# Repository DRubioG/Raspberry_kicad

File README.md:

# Raspberry_kicad
 Raspberry  Pi 4 in Kicad

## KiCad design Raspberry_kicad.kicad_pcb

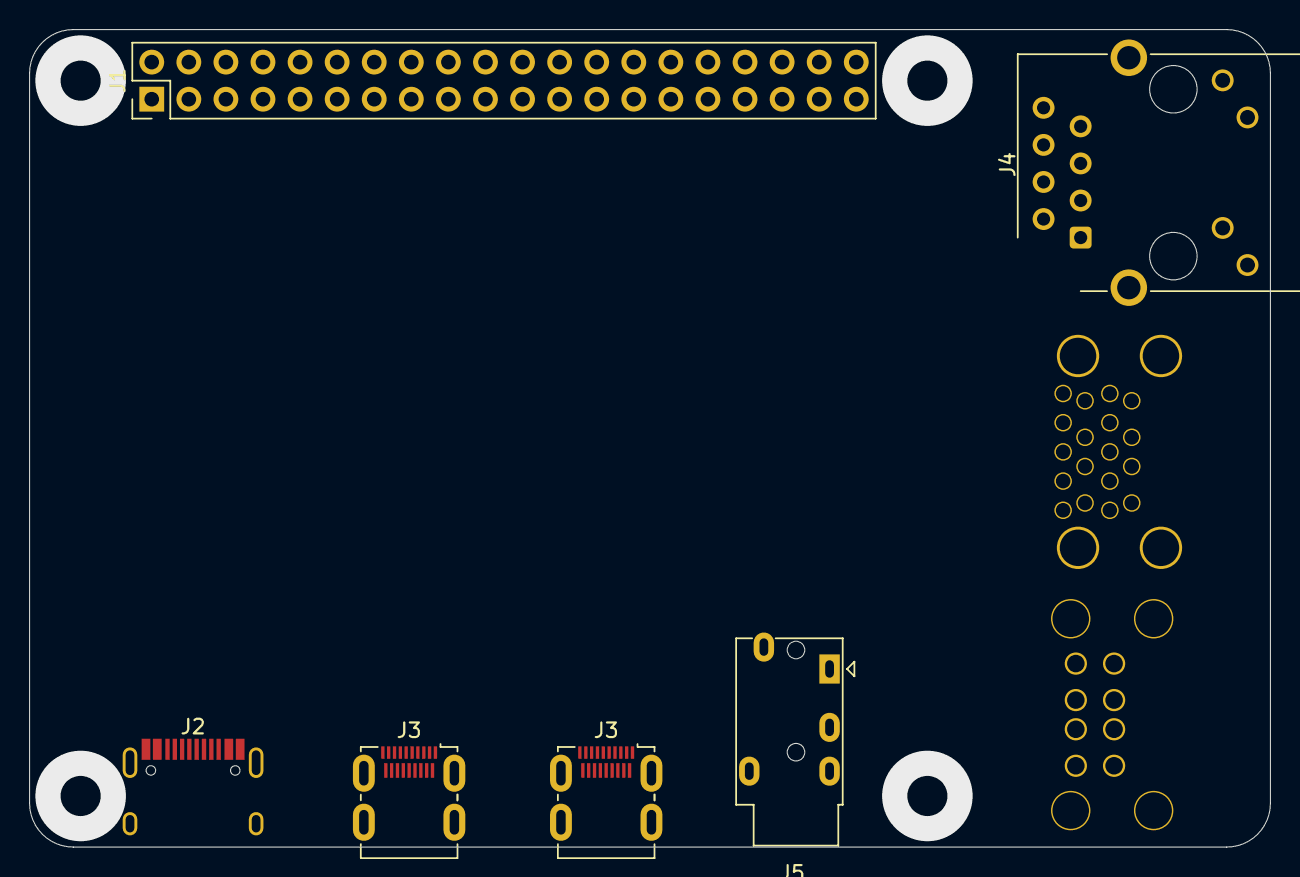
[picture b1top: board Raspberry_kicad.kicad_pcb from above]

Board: 2 copper layers, 85.0 x 56.0 mm, 9 parts (1 on the bottom side), 20 nets, no tracks yet.

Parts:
J1: Conn_02x20_Top_Bottom; PinHeader_2x20_P2.54mm_Vertical
J2: usb_type_c; HRO-TYPE-C-31-M-12-Assembly
J3, J3#2: HDMI_D_1.4; HDMI_Micro-D_Molex_46765-1x01
J4: RJ45_LED; RJ45_Cetus_J1B1211CCD_Horizontal
J5: AudioJack4_Ground; Jack_3.5mm_PJ320E_Horizontal
J6: Micro_SD_Card; microSD_HC_Molex_104031-0811
U1: USB_3_0_HUB; MOLES_USB_3_0_HUB
U2: USB_2_0_HUB; MOLEX_USB_2_0_HUB

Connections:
unnamed: J3.1, J3#2.1
unnamed: J3.2, J3#2.2
unnamed: J3.3, J3#2.3
unnamed: J3.4, J3#2.4
unnamed: J3.5, J3#2.5
unnamed: J3.6, J3#2.6
unnamed: J3.7, J3#2.7
unnamed: J3.8, J3#2.8
unnamed: J3.9, J3#2.9
unnamed: J3.10, J3#2.10
unnamed: J3.11, J3#2.11
unnamed: J3.12, J3#2.12
unnamed: J3.13, J3#2.13
unnamed: J3.14, J3#2.14
unnamed: J3.15, J3#2.15
unnamed: J3.16, J3#2.16
unnamed: J3.17, J3#2.17
unnamed: J3.18, J3#2.18
unnamed: J3.19, J3#2.19
unnamed: J3.SH, J3#2.SH

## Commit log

2021-04-07 template
    template info
